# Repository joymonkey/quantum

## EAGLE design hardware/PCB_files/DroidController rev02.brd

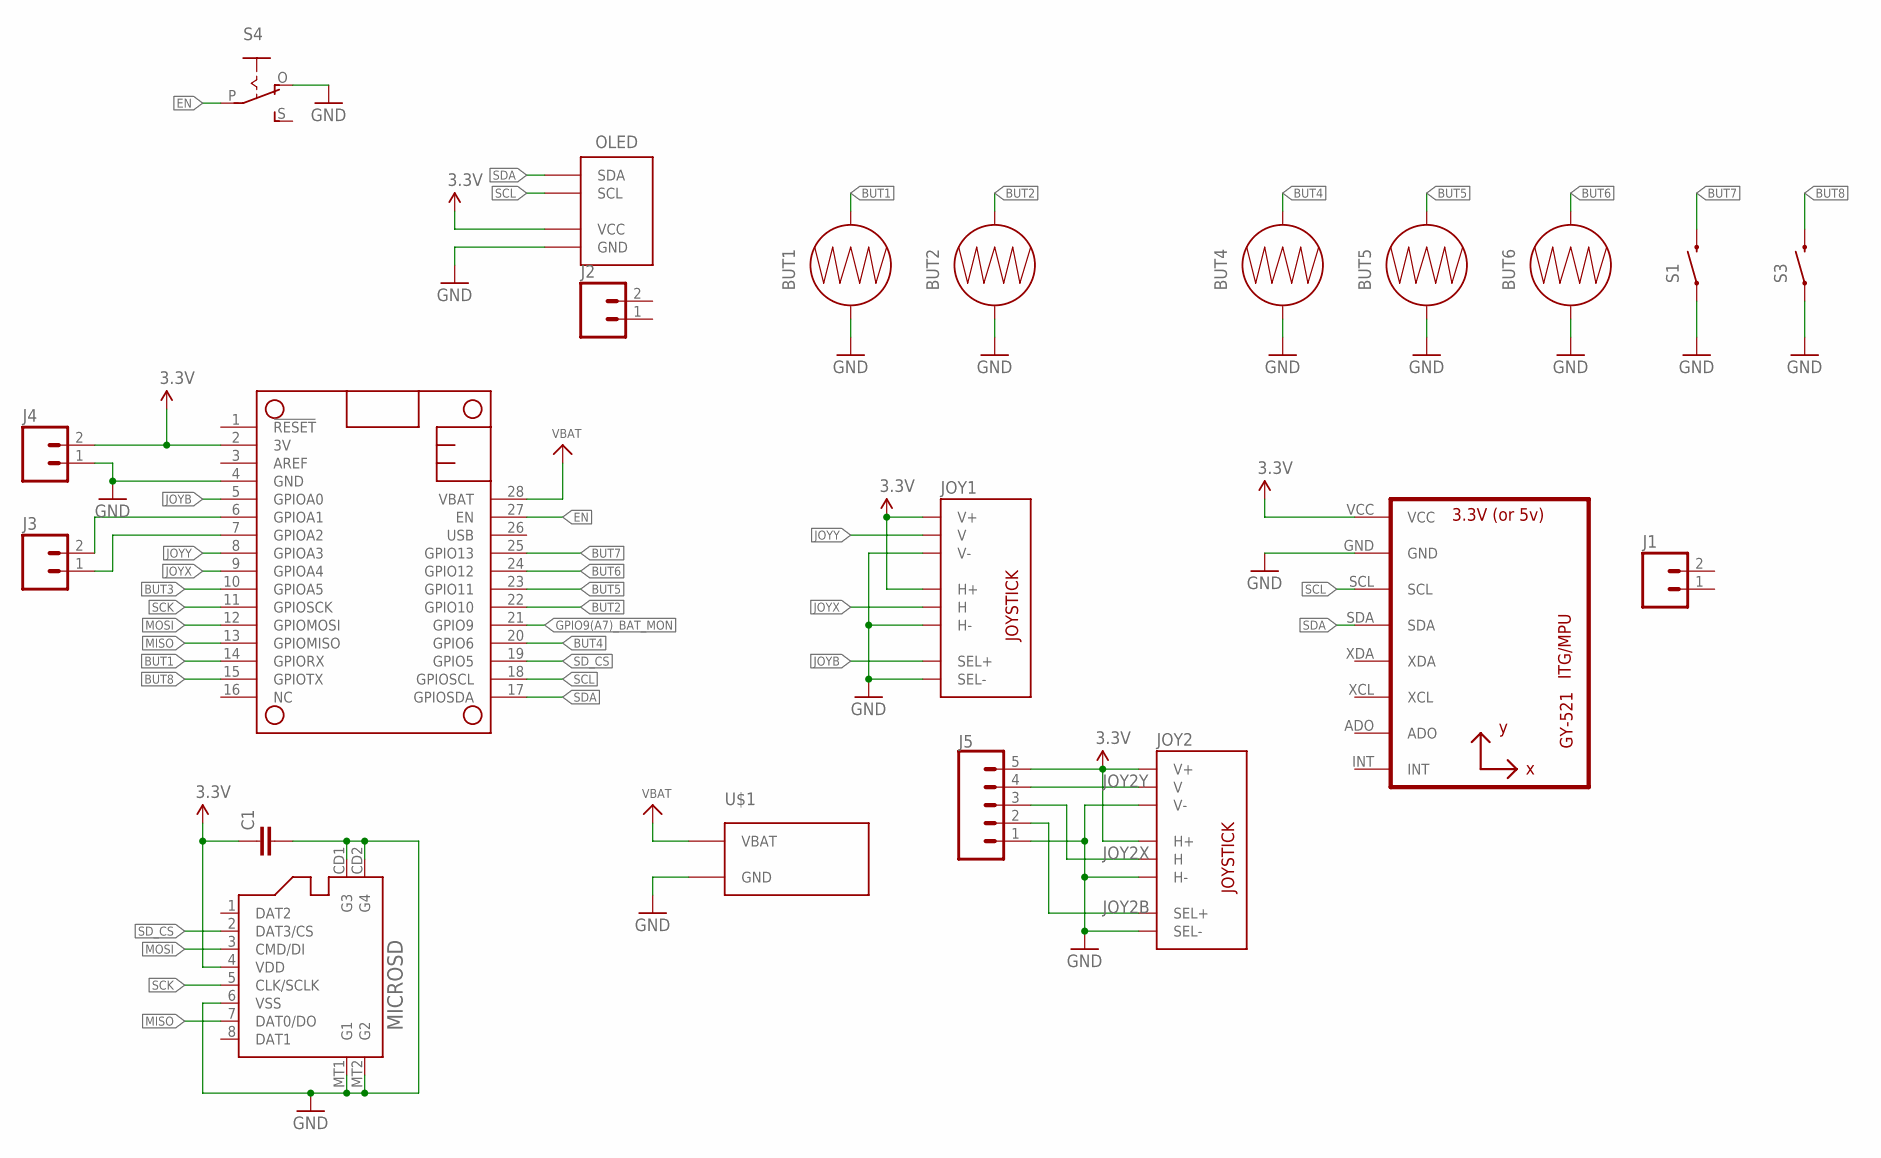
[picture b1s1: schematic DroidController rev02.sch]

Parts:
BUT1, BUT2, BUT4, BUT5, BUT6: BUTTON-CONDUCTIVEBUTTON-COND2; BUTTON-CONDUCTIVE2
C1: C-EUC0603; C0603
J1, J2, J3, J4: M02PTH; 1X02
J5: CONN_05; 1X05
JOY1, JOY2: JOYSTICK; JOYSTICK_SM
MICROSD: MICROSD; MICROSD_SMALL
MS1: FEATHERWING_NODIM; FEATHERWING_DIM
OLED: SH1106_I2C; SH1106_128X32
S1, S3: SWITCH-MOMENTARY-2SIDE_EZ; TACTILE-PTH-SIDEEZ
S4: EG1218S; EG1218
U2: GY-521MPU6050; GY-521
U$1: KEYSTONE_BAT; 1042

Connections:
3.3V: C1.1, J4.2, J5.5, JOY1.H1 (H+), JOY1.V1 (V+), JOY2.H1 (H+), JOY2.V1 (V+), MICROSD.4 (VDD), MS1.2 (3V), OLED.VCC, U2.VCC
BUT1: BUT1.2, MS1.14 (GPIORX)
BUT2: BUT2.2, MS1.22 (GPIO10)
BUT3: MS1.10 (GPIOA5)
BUT4: BUT4.2, MS1.20 (GPIO6)
BUT5: BUT5.2, MS1.23 (GPIO11)
BUT6: BUT6.2, MS1.24 (GPIO12)
BUT7: MS1.25 (GPIO13), S1.2
BUT8: MS1.15 (GPIOTX), S3.2
EN: MS1.27 (EN), S4.P
GND: BUT1.1, BUT2.1, BUT4.1, BUT5.1, BUT6.1, C1.2, J4.1, J5.1, JOY1.B2A (SEL-), JOY1.H3 (H-), JOY1.V3 (V-), JOY2.B2A (SEL-), JOY2.H3 (H-), JOY2.V3 (V-), MICROSD.6 (VSS), MICROSD.CD1 (G3), MICROSD.CD2 (G4), MICROSD.MT1 (G1), MICROSD.MT2 (G2), MS1.4 (GND), OLED.GND, S1.1, S3.1, S4.O, U2.GND, U$1.GND
GPIO9(A7)_BAT_MON: MS1.21 (GPIO9)
JOY2B: J5.2, JOY2.B1A (SEL+)
JOY2X: J5.3, JOY2.H2 (H)
JOY2Y: J5.4, JOY2.V2 (V)
JOYB: JOY1.B1A (SEL+), MS1.5 (GPIOA0)
JOYX: JOY1.H2 (H), MS1.9 (GPIOA4)
JOYY: JOY1.V2 (V), MS1.8 (GPIOA3)
MISO: MICROSD.7 (DAT0/DO), MS1.13 (GPIOMISO)
MOSI: MICROSD.3 (CMD/DI), MS1.12 (GPIOMOSI)
unnamed: J3.2, MS1.6 (GPIOA1)
unnamed: J3.1, MS1.7 (GPIOA2)
SCK: MICROSD.5 (CLK/SCLK), MS1.11 (GPIOSCK)
SCL: MS1.18 (GPIOSCL), OLED.SCL, U2.SCL
SDA: MS1.17 (GPIOSDA), OLED.SDA, U2.SDA
SD_CS: MICROSD.2 (DAT3/CS), MS1.19 (GPIO5)
VBAT: MS1.28 (VBAT), U$1.VBAT

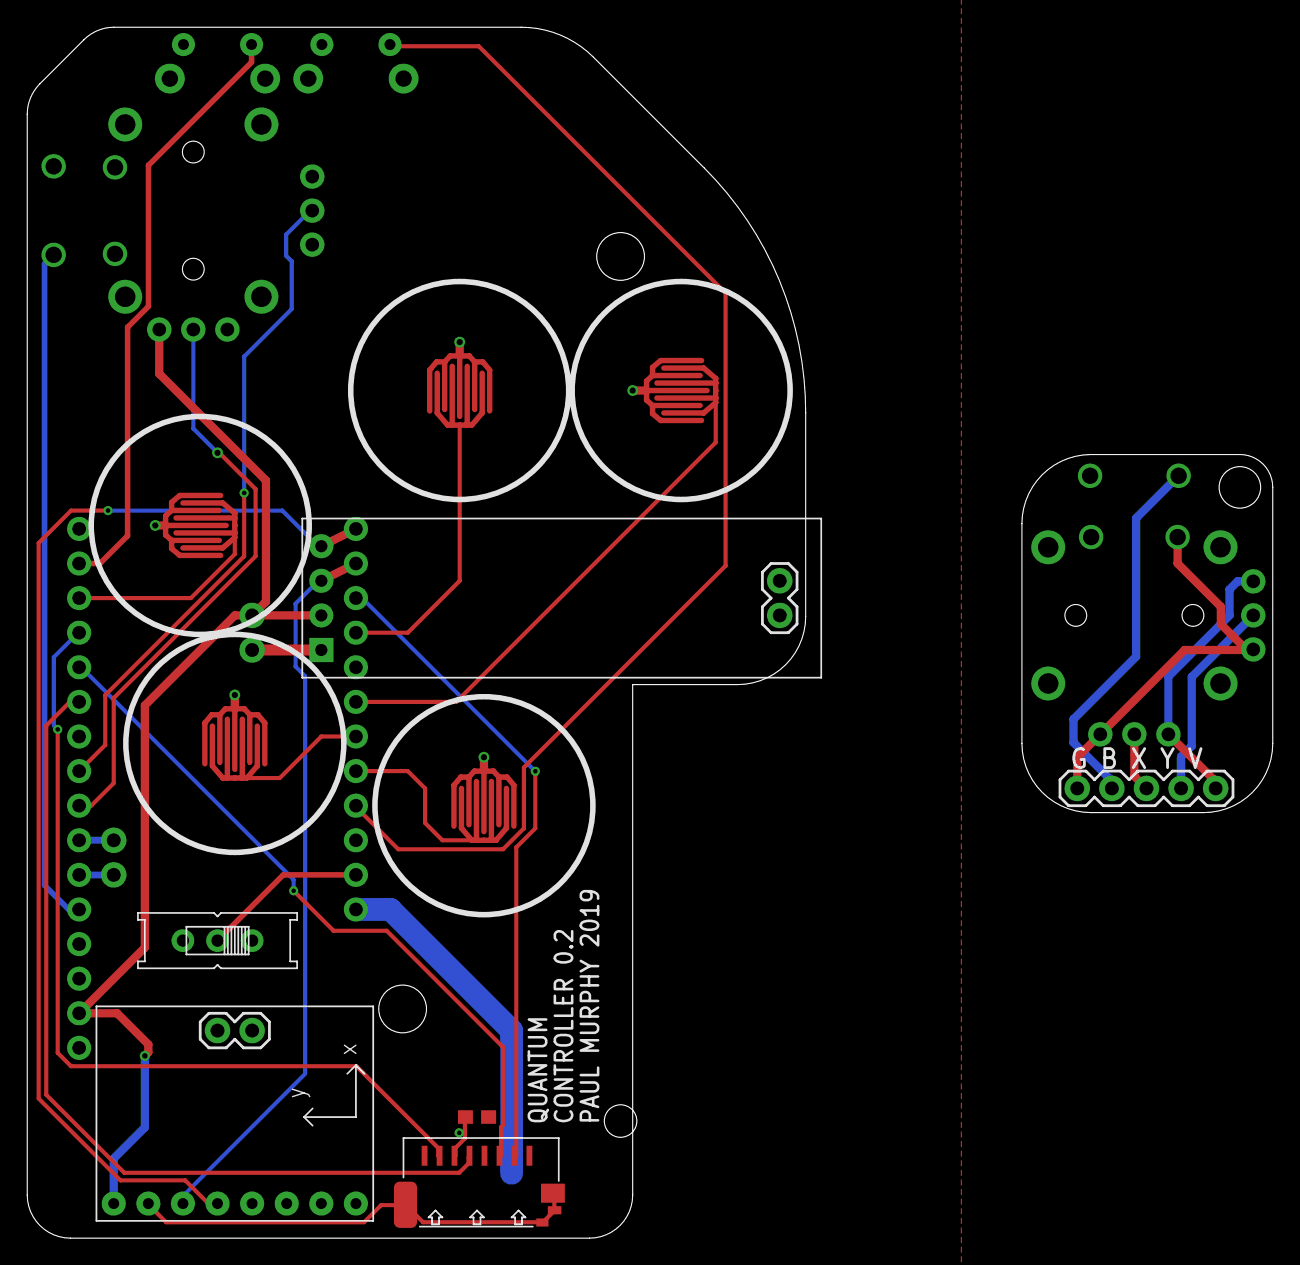
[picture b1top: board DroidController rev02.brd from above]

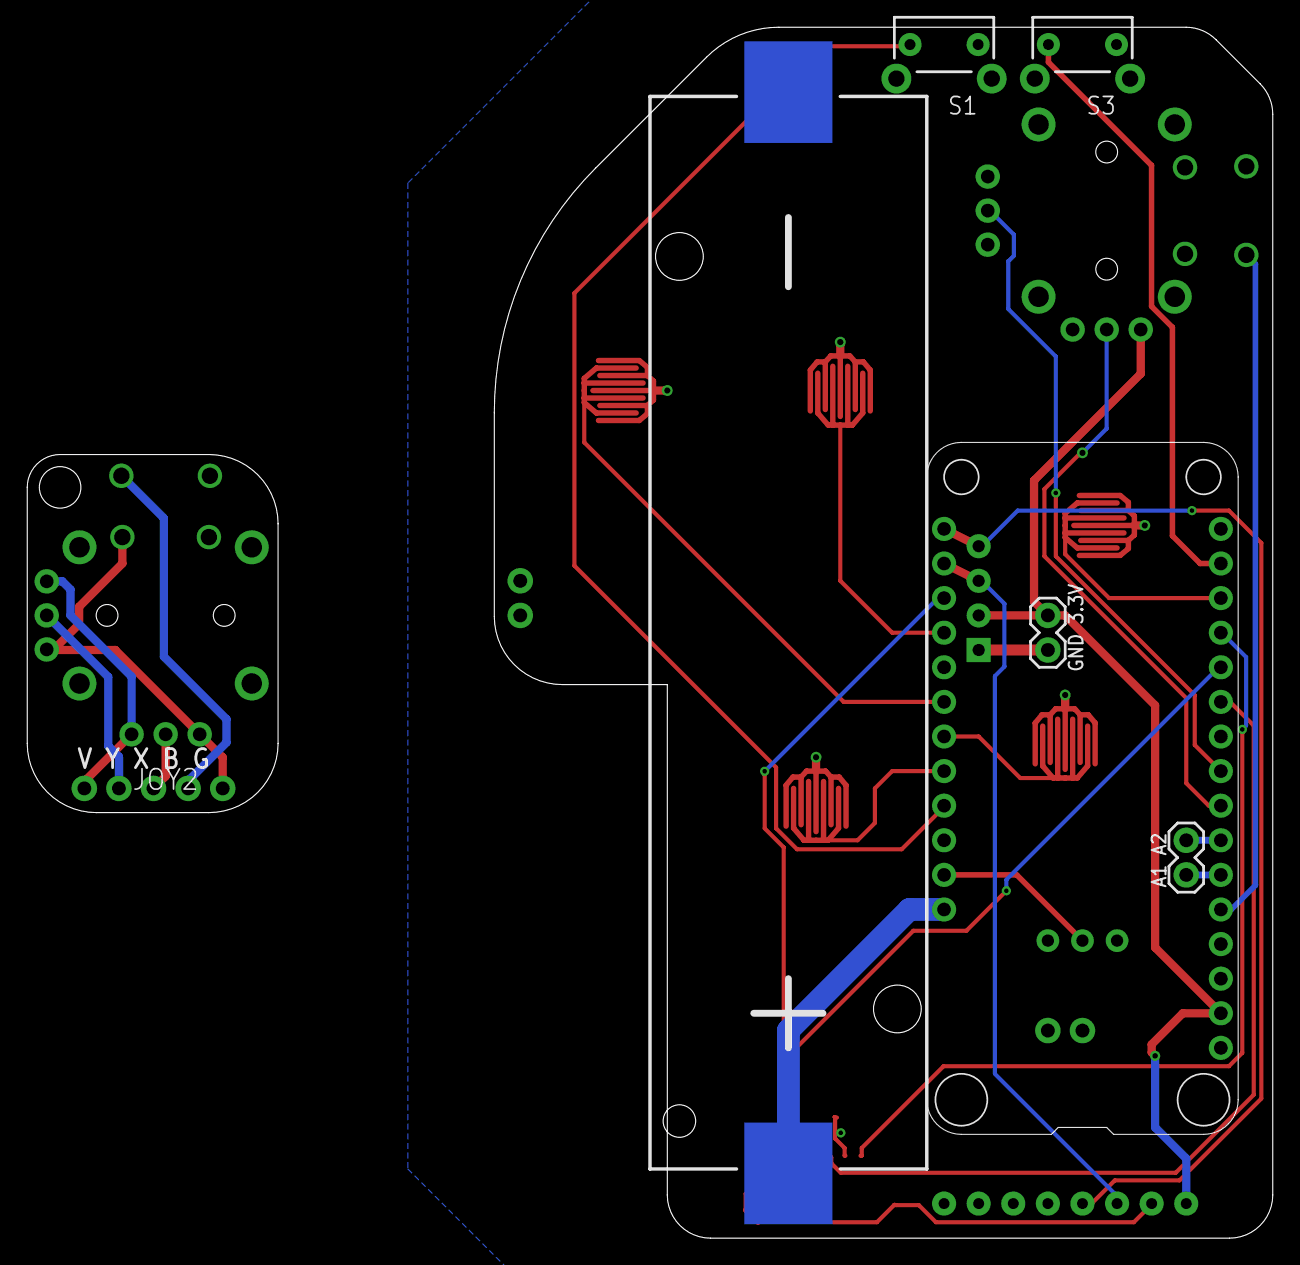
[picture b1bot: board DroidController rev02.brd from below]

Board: 2 copper layers, 91.4 x 88.9 mm, 21 parts (7 on the bottom side), 25 nets.

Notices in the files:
parts and their libraries:
SparkFun-Electromechanical: Licensing: Creative Commons ShareAlike 4.0 International - https://creativecommons.org/licenses/by-sa/4.0
microbuilder: This work is placed in the public domain, and may be freely used for commercial and non-commercial work with the following conditions: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
